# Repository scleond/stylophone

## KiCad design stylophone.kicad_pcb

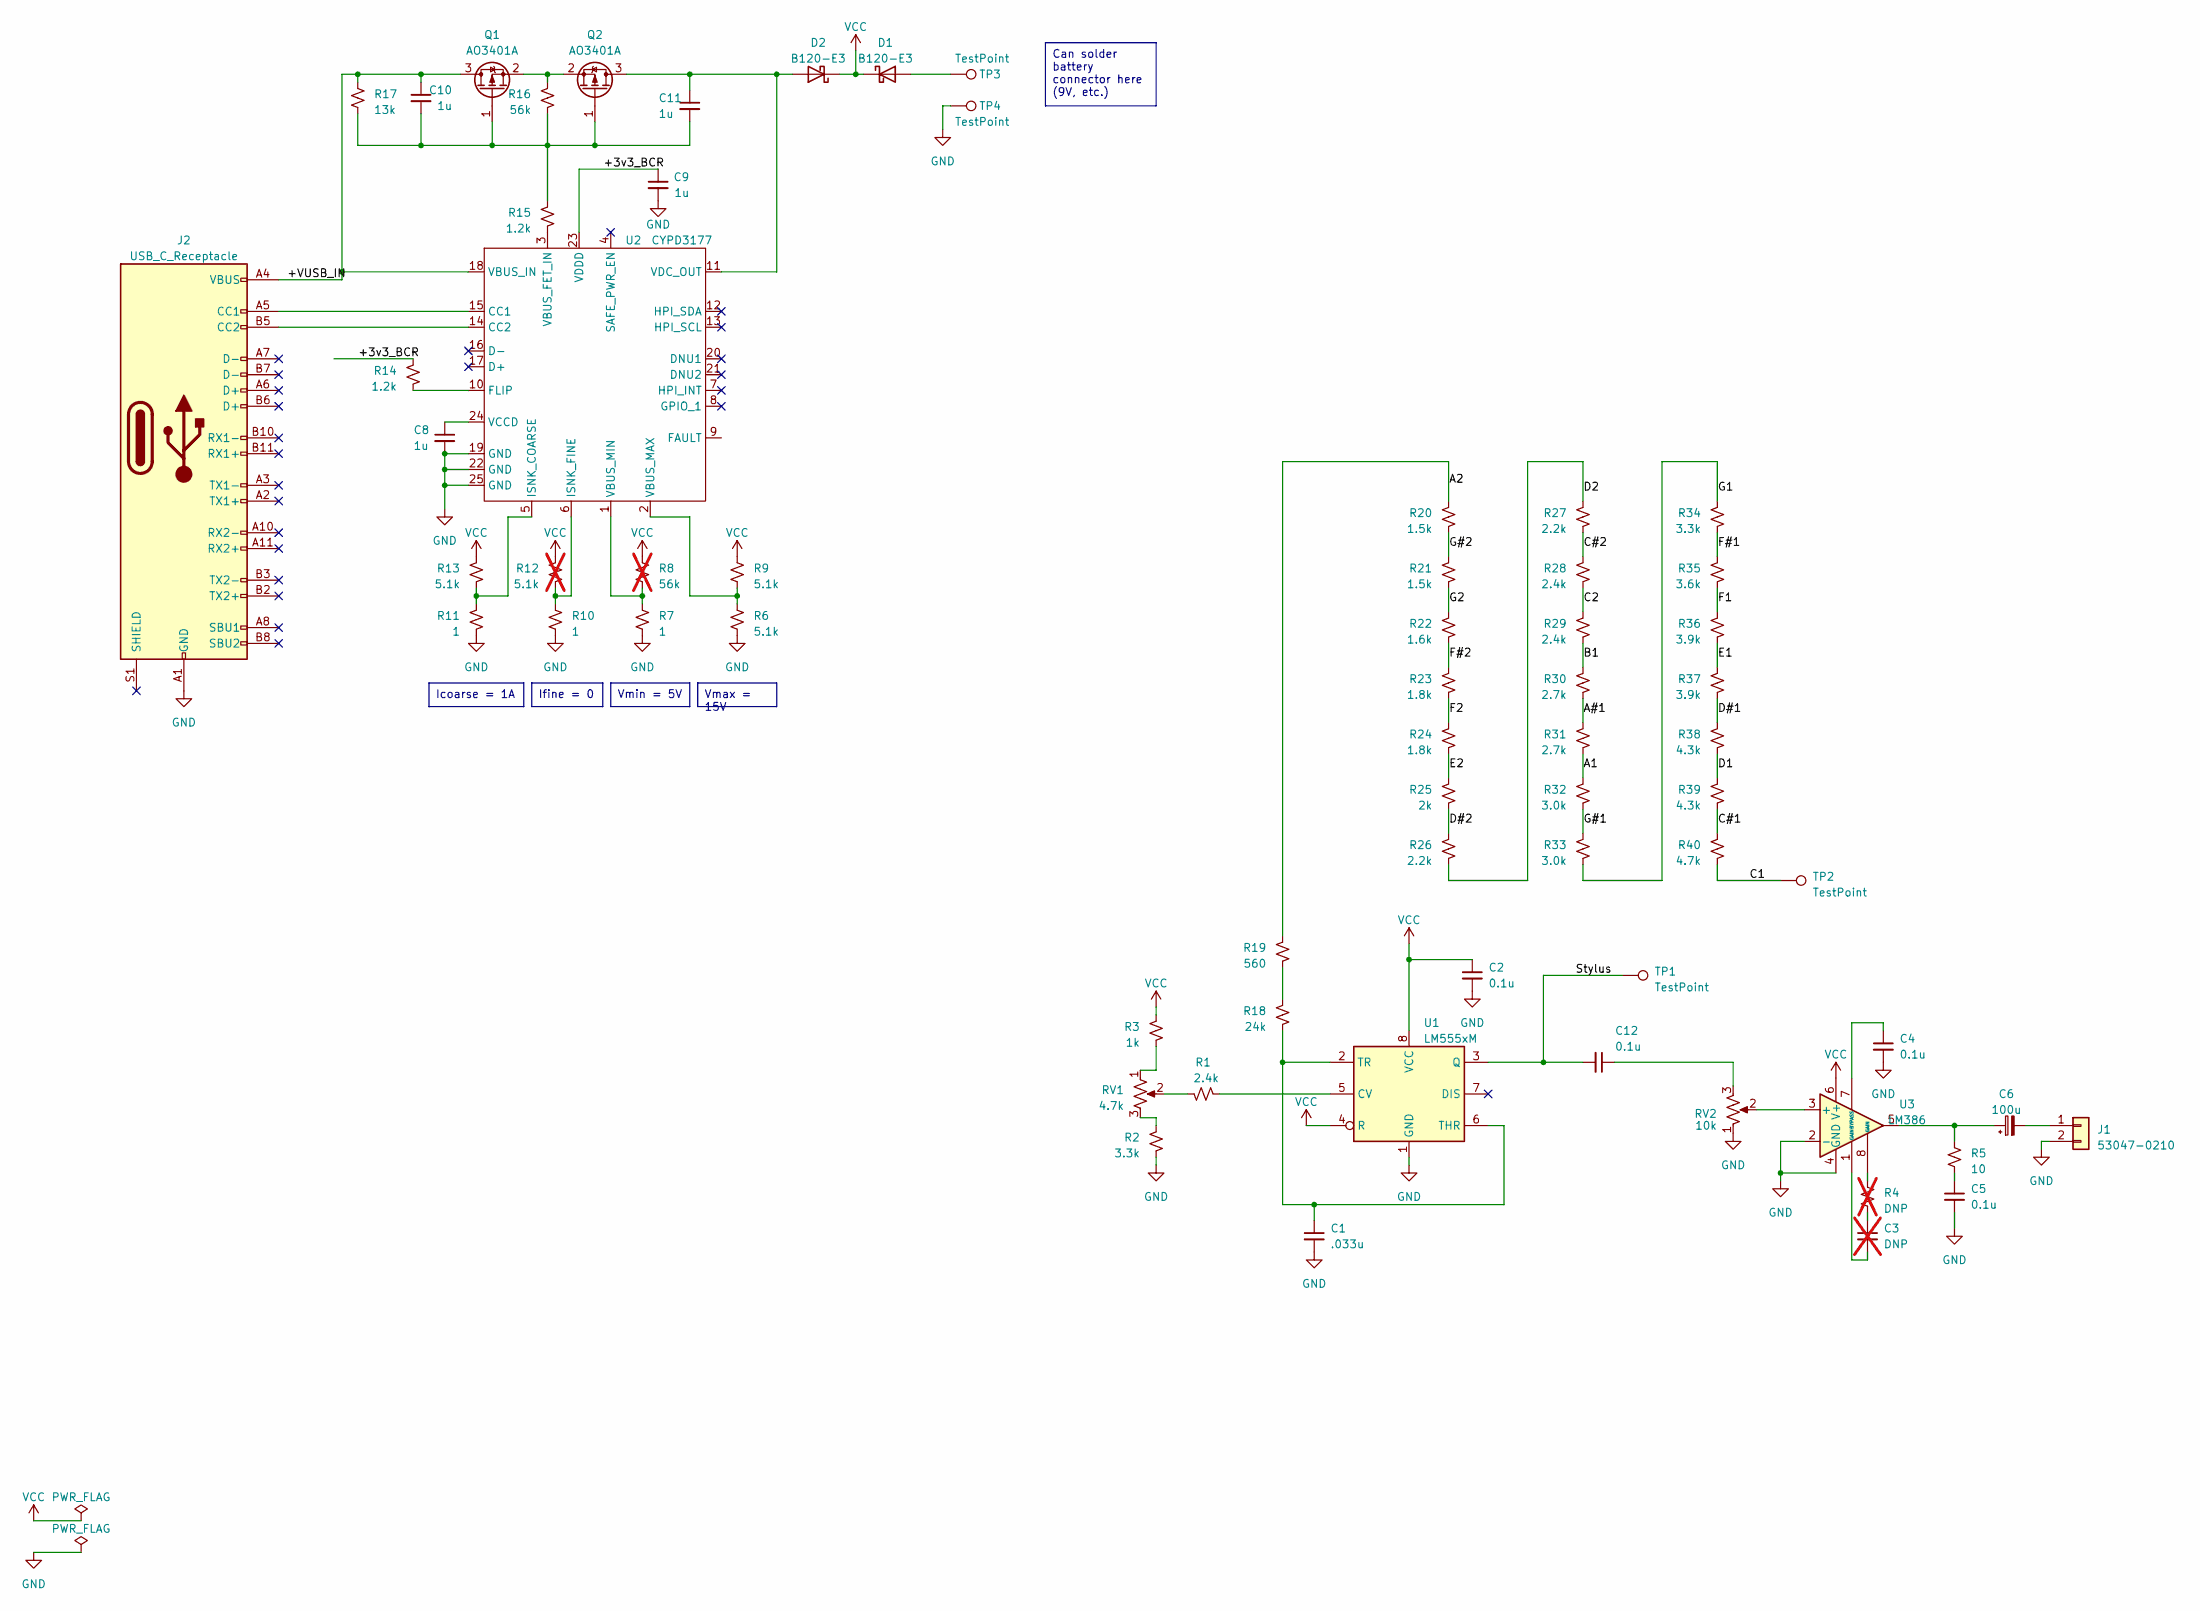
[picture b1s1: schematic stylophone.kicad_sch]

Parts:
C1: .033u; C_0603_1608Metric
C2, C4, C5, C12: 0.1u; C_0603_1608Metric
C3: DNP; C_0603_1608Metric; not fitted
C6: 100u; CP_Elec_8x6.2
C8, C9, C10, C11: 1u; C_0603_1608Metric
D1, D2: B120-E3; D_SMA
J1: 53047-0210; Molex_PicoBlade_53047-0210_1x02_P1.25mm_Vertical
J2: USB_C_Receptacle; USB_C_Receptacle_Molex_105450-0101
Q1, Q2: AO3401A; SOT-23
R1, R28, R29: 2.4k; R_0603_1608Metric
R2, R34: 3.3k; R_0603_1608Metric
R3: 1k; R_0603_1608Metric
R4: DNP; R_0603_1608Metric; not fitted
R5: 10; R_0603_1608Metric
R6, R9, R13: 5.1k; R_0603_1608Metric
R7, R10, R11: 1; R_0603_1608Metric
R8: 56k; R_0603_1608Metric; not fitted
R12: 5.1k; R_0603_1608Metric; not fitted
R14, R15: 1.2k; R_0603_1608Metric
R16: 56k; R_0603_1608Metric
R17: 13k; R_0603_1608Metric
R18: 24k; R_0603_1608Metric
R19: 560; R_0603_1608Metric
R20, R21: 1.5k; R_0603_1608Metric
R22: 1.6k; R_0603_1608Metric
R23, R24: 1.8k; R_0603_1608Metric
R25: 2k; R_0603_1608Metric
R26, R27: 2.2k; R_0603_1608Metric
R30, R31: 2.7k; R_0603_1608Metric
R32, R33: 3.0k; R_0603_1608Metric
R35: 3.6k; R_0603_1608Metric
R36, R37: 3.9k; R_0603_1608Metric
R38, R39: 4.3k; R_0603_1608Metric
R40: 4.7k; R_0603_1608Metric
RV1: 4.7k; Potentiometer_Piher_T-16H_Single_Horizontal
RV2: 10k; Potentiometer_Piher_T-16H_Single_Horizontal
TP1, TP2, TP3, TP4: TestPoint; TestPoint_THTPad_D1.5mm_Drill0.7mm
U1: LM555xM; SOIC-8_3.9x4.9mm_P1.27mm
U2: CYPD3177; QFN-24-1EP_4x4mm_P0.5mm_EP2.15x2.15mm
U3: LM386; SOIC-8_3.9x4.9mm_P1.27mm

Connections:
/+3v3_BCR: C9.1, R14.2, U2.23 (VDDD)
/+VUSB_IN: C10.1, J2.A4 (VBUS), J2.A9 (VBUS), J2.B4 (VBUS), J2.B9 (VBUS), Q1.3 (D), R17.2, U2.18 (VBUS_IN)
/A1: R31.1, R32.2
/A2: R19.2, R20.2
/A#1: R30.1, R31.2
/B1: R29.1, R30.2
/C1: R40.1, TP2.1
/C2: R28.1, R29.2
/C#1: R39.1, R40.2
/C#2: R27.1, R28.2
/D1: R38.1, R39.2
/D2: R26.1, R27.2
/D#1: R37.1, R38.2
/D#2: R25.1, R26.2
/E1: R36.1, R37.2
/E2: R24.1, R25.2
/F1: R35.1, R36.2
/F2: R23.1, R24.2
/F#1: R34.1, R35.2
/F#2: R22.1, R23.2
/G1: R33.1, R34.2
/G2: R21.1, R22.2
/G#1: R32.1, R33.2
/G#2: R20.1, R21.2
/Stylus: C12.2, TP1.1, U1.3 (Q)
GND: C1.2, C2.2, C4.2, C5.2, C8.2, C9.2, J1.2, J2.A1 (GND), J2.A12 (GND), J2.B1 (GND), J2.B12 (GND), R2.1, R6.1, R7.1, R10.1, R11.1, RV2.1, TP4.1, U1.1 (GND), U2.19 (GND), U2.22 (GND), U2.25 (GND), U3.2 (-), U3.4 (GND)
unnamed: C3.1, R4.1
unnamed: C3.2, U3.1 (GAIN)
unnamed: C5.1, R5.1
unnamed: C6.1, R5.2, U3.5
unnamed: C12.1, RV2.3
unnamed: D1.2 (A), TP3.1
unnamed: C11.1, D2.2 (A), Q2.3 (D), U2.11 (VDC_OUT)
unnamed: C6.2, J1.1
unnamed: J2.A5 (CC1), U2.15 (CC1)
unnamed: J2.B5 (CC2), U2.14 (CC2)
unnamed: C10.2, C11.2, Q1.1 (G), Q2.1 (G), R15.2, R16.1, R17.1
unnamed: Q1.2 (S), Q2.2 (S), R16.2
unnamed: R1.2, RV1.2
unnamed: R2.2, RV1.3
unnamed: R3.1, RV1.1
unnamed: R4.2, U3.8 (GAIN)
unnamed: R18.2, R19.1
unnamed: R1.1, U1.5 (CV)
unnamed: C1.1, R18.1, U1.2 (TR), U1.6 (THR)
unnamed: R14.1, U2.10 (FLIP)
unnamed: R11.2, R13.1, U2.5 (ISNK_COARSE)
unnamed: R10.2, R12.1, U2.6 (ISNK_FINE)
unnamed: R15.1, U2.3 (VBUS_FET_IN)
unnamed: R6.2, R9.1, U2.2 (VBUS_MAX)
unnamed: R7.2, R8.1, U2.1 (VBUS_MIN)
unnamed: C8.1, U2.24 (VCCD)
unnamed: RV2.2, U3.3 (+)
unnamed: C4.1, U3.7 (BYPASS)
VCC: C2.1, D1.1 (K), D2.1 (K), R3.2, R8.2, R9.2, R12.2, R13.2, U1.4 (R), U1.8 (VCC), U3.6 (V+)

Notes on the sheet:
Can solder battery connector here (9V, etc.)
Ifine = 0
Vmin = 5V
Vmax = 15V
Icoarse = 1A

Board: 2 copper layers, 66 parts (0 on the bottom side), 55 nets, no tracks yet.

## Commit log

2024-02-06 Updated all values and footprints
2024-02-07 updated 3d models
